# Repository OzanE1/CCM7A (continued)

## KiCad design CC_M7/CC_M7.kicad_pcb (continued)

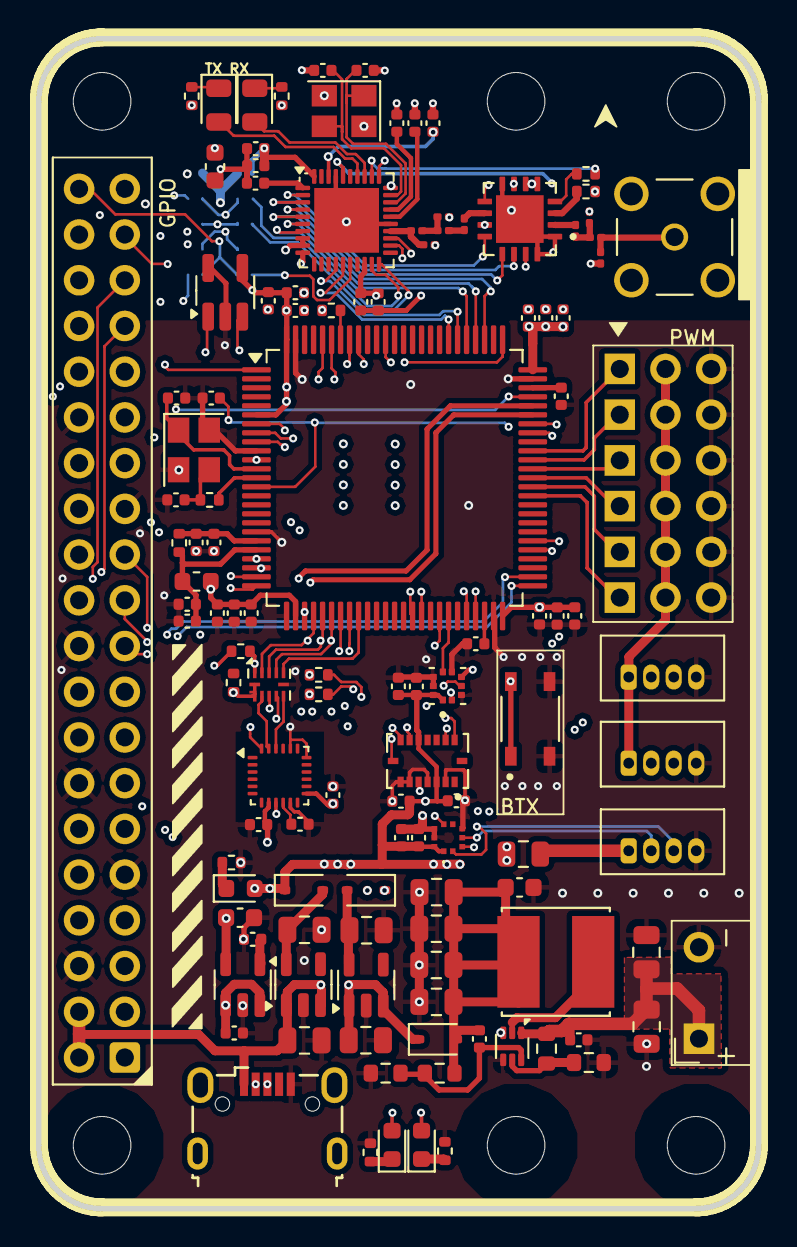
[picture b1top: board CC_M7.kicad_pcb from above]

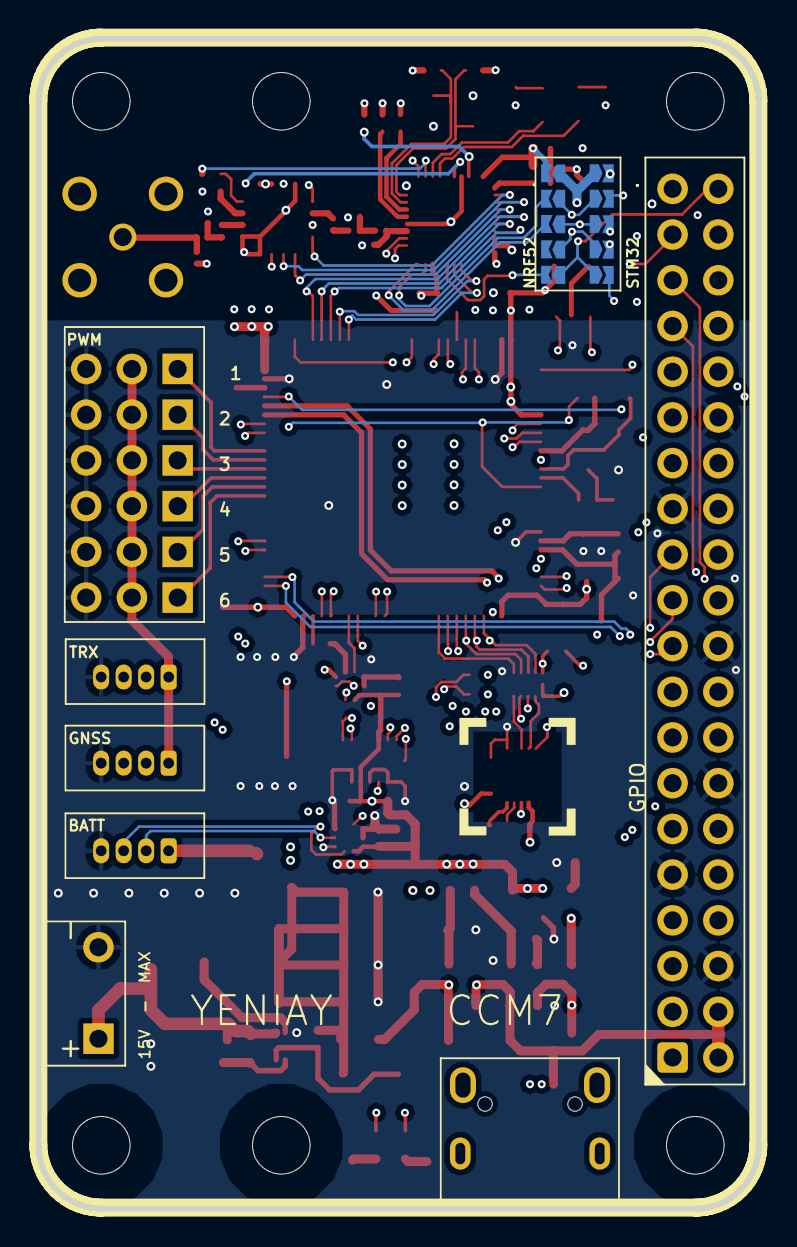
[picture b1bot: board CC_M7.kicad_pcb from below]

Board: 4 copper layers, 40.0 x 65.0 mm, 140 parts (10 on the bottom side), 112 nets.

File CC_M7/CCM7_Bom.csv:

"Reference","Value","Datasheet","Footprint","Qty","DNP"
"C1,C43,C57","10uF","~","-- mixed values --","3",""
"C2,C3,C4,C5,C6,C7,C8,C9,C10,C11,C12,C14,C16,C19,C22,C23,C24,C25,C26,C27,C33,C38,C41,C42,C47,C48,C54,C55","100nF","~","-- mixed values --","28",""
"C13,C15,C30,C36,C39,C45,C46,C50","1uF","~","-- mixed values --","8",""
"C17,C18","2.2uF","~","Capacitor_SMD:C_0603_1608Metric","2",""
"C20,C21,C32,C44","12pF","~","Capacitor_SMD:C_0603_1608Metric","4",""
"C28","2pF","~","Capacitor_SMD:C_0201_0603Metric","1",""
"C29","1pF","~","Capacitor_SMD:C_0201_0603Metric","1",""
"C31","100pF","~","Capacitor_SMD:C_0603_1608Metric","1",""
"C34,C40","4.7uF","~","Capacitor_SMD:C_0603_1608Metric","2",""
"C35","820pF","~","Capacitor_SMD:C_0603_1608Metric","1",""
"C37","47nF","~","Capacitor_SMD:C_0603_1608Metric","1",""
"C49","47pF","~","Capacitor_SMD:C_0603_1608Metric","1",""
"C51,C52,C53","C_Small","~","Capacitor_SMD:C_0603_1608Metric","3",""
"C56","22uF","~","Capacitor_SMD:C_0805_2012Metric","1",""
"D1","MBR230LSFT1G","","MBR230LSFT1G:SODFL3619X98N","1",""
"D3,D4,D5,D6","LED","~","LED_SMD:LED_0603_1608Metric","4",""
"F1","Polyfuse","~","Fuse:Fuse_1206_3216Metric","1",""
"FB1","FerriteBead","~","Inductor_SMD:L_0603_1608Metric","1",""
"J1,J10,J12","Conn_01x04_Pin","~","Connector_Hirose:Hirose_DF13-04P-1.25DSA_1x04_P1.25mm_Vertical","3",""
"J2","~","~","Connector_IDC:IDC-Header_2x20_P2.54mm_Vertical","1",""
"J3,J4,J5,J6,J7,J8","Conn_01x03_Pin","~","Connector_PinHeader_2.54mm:PinHeader_1x03_P2.54mm_Vertical","6",""
"J9","SMA_CONNECTOR","","LPRS_SMA_CONNECTOR:LPRS_SMA_CONNECTOR","1",""
"J11","USB_B_Micro","~","Connector_USB:USB_Micro-B_Wuerth_629105150521","1",""
"J13","Batt_Pins","~","Connector_PinSocket_2.54mm:PinSocket_1x02_P2.54mm_Vertical","1",""
"JP1,JP2,JP3,JP4,JP5,JP6,JP7,JP8","SWDIO","~","Capacitor_SMD:C_0201_0603Metric","8",""
"L1","10uH","~","Inductor_SMD:L_0603_1608Metric","1",""
"L2","15nH","~","Inductor_SMD:L_0603_1608Metric","1",""
"L3","3.3uH","~","Inductor_SMD:L_Changjiang_FXL0650","1",""
"L6","1.9nH","~","Inductor_SMD:L_0201_0603Metric","1",""
"L7","3.0nH","~","Inductor_SMD:L_0201_0603Metric","1",""
"R1","4k7","~","Resistor_SMD:R_0603_1608Metric","1",""
"R2,R8,R9,R17","1.5k","~","Resistor_SMD:R_0603_1608Metric","4",""
"R3","620R","~","Resistor_SMD:R_0603_1608Metric","1",""
"R4,R5","4.7k","~","Resistor_SMD:R_0603_1608Metric","2",""
"R10","100K","~","Resistor_SMD:R_0603_1608Metric","1",""
"R11","1k","~","Resistor_SMD:R_0603_1608Metric","1",""
"R12","220K","~","Resistor_SMD:R_0603_1608Metric","1",""
"R13","30K","~","Resistor_SMD:R_0603_1608Metric","1",""
"R15","10k","~","Resistor_SMD:R_0603_1608Metric","1",""
"R16","50R","~","Resistor_SMD:R_0603_1608Metric","1",""
"S1","SKRPABE010","","SW_SKRPABE010:SW_SKRPABE010","1",""
"U1","STM32H743VITx","https://www.st.com/resource/en/datasheet/stm32h743vi.pdf","Package_QFP:LQFP-100_14x14mm_P0.5mm","1",""
"U2","24AA64T-I/OT","24AA64T-I/OT","Package_TO_SOT_SMD:SOT-23-5_HandSoldering","1",""
"U3","BMI088","","BMI088:PQFN50P450X300X100-16N","1",""
"U4","ICP-20100","","ICP-20100:PQFN50P200X200X85-10N","1",""
"U5","BMM150","https://www.mouser.com/datasheet/2/783/BST-BMM150-DS001-01-7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","Package_CSP:WLCSP-12_1.56x1.56mm_P0.4mm","1",""
"U6","nRF52820-QDxx","https://infocenter.nordicsemi.com/pdf/nRF52820_PS_v1.0.pdf","Package_DFN_QFN:QFN-40-1EP_5x5mm_P0.4mm_EP3.6x3.6mm","1",""
"U7","NRF21540-QDAA-R7","","nRF21540:QFN65P400X400X95-17N","1",""
"U8","TPS562246DRLR","TPS562246DRLR","TPS562246DRLR:DRL0006A-MFG","1",""
"U9,U10","ME6211C33M5","https://www.lcsc.com/datasheet/lcsc_datasheet_2304140030_MIC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","Package_TO_SOT_SMD:SOT-23-5","2",""
"U11","BMP581","","BMP581:BMP581","1",""
"U12","IIM-42652","https://invensense.tdk.com/wp-content/uploads/2021/01/ds-000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","Package_LGA:Bosch_LGA-14_3x2.5mm_P0.5mm","1",""
"Y1,Y2","32MHz","~","Crystal:Crystal_SMD_3225-4Pin_3.2x2.5mm","2",""

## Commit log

2025-05-09 readme
2025-05-09 add files.
2025-05-09 test
2025-05-09 New regulator tps566242DRL
2025-05-09 Scehmatic completed.
2025-05-09 last control
2025-05-10 CCM7A docx Updated
2025-05-11 ready for routing
2025-05-11 ready to routing
2025-05-11 ready final
2025-05-12 Routing in progress
2025-05-12 Inductor added.
2025-05-13 CCM7A Routing in progress.
2025-05-13 regülatör devresi güvenli kullanıma uygun hale getirildi.
2025-05-13 CCM7A BIG ROUTING PROGRESS
2025-05-15 error check
2025-05-18 Debugging routes added. / Debug footprint updated.
2025-05-18 bom added
2025-05-19 Routing Completed 0 Error
2025-05-19 BOM finished.
2025-05-19 Rotation check completed.
2025-05-24 Routing Update
2025-05-25 last check
2025-05-25 Finished
2025-06-01 vias constraints changes
2025-06-01 via correction completed
2025-06-05 CCM7 Unconnected item routing progress.
2025-06-26 pdf added
